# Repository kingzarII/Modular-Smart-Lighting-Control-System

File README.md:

# Modular-Smart-Lighting-Control-System

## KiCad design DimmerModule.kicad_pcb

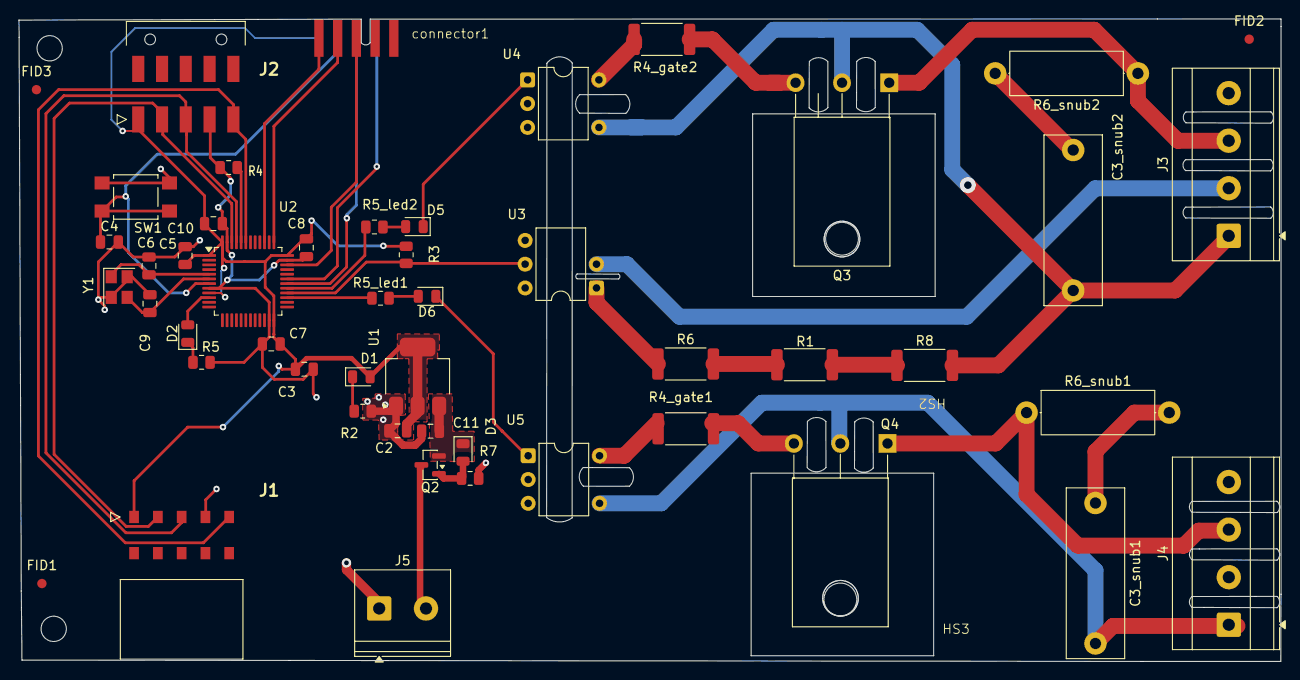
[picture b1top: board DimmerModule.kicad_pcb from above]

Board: 2 copper layers, 134.8 x 68.6 mm, 54 parts (0 on the bottom side), 41 nets.

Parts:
C2, C11: 22u; C_0805_2012Metric
C3: 10uF; C_0805_2012Metric
C3_snub1, C3_snub2: 100nF; C_Rect_L18.0mm_W6.0mm_P15.00mm_FKS3_FKP3
C4, C5, C7, C8: 100nF; C_0805_2012Metric
C6, C9: 10pF; C_0805_2012Metric
C10: 100n; C_0805_2012Metric
D1: LED; D_0805_2012Metric
D2: LED; LED_0805_2012Metric
D3: D_Zener; D_0805_2012Metric
D5, D6: RED; LED_0805_2012Metric
FID1, FID2, FID3: Fiducial; Fiducial_1mm_Mask2mm
H1, H1#2: MountingHole; MountingHole_2.7mm_M2.5
HS2, HS3: Heatsink; cooler
J1: Conn_01x05_Socket; 1156901
J2: Conn_01x05_Pin; 1156939
J3, J4: Screw_Terminal_01x04; TerminalBlock_Phoenix_MKDS-3-4-5.08_1x04_P5.08mm_Horizontal
J5: Screw_Terminal_01x02; TerminalBlock_Phoenix_PT-1,5-2-5.0-H_1x02_P5.00mm_Horizontal
Q2: AO3401A; SOT-23
Q3, Q4: BTA16-800B; TO-220-3_Horizontal_TabDown
R1, R8: 15KΩ; R_2512_6332Metric
R2, R5: 1.5K; R_0805_2012Metric
R3: 10kΩ; R_0805_2012Metric
R4, R7: 10K; R_0805_2012Metric
R4_gate1, R4_gate2: 180Ω; R_2512_6332Metric
R5_led1, R5_led2: 150Ω; R_0805_2012Metric
R6: 15kΩ; R_2512_6332Metric
R6_snub1, R6_snub2: 100Ω; R_Axial_DIN0414_L11.9mm_D4.5mm_P15.24mm_Horizontal
SW1: SW_Push; SW_SPST_TL3305B
U1: AMS1117-3.3; SOT-223-3_TabPin2
U2: STM32F103C8T6; LQFP-48_7x7mm_P0.5mm
U3: H11AA1; DIP-6_W7.62mm
U4, U5: MOC3021M; DIP-6_W7.62mm
Y1: 16Mhz; Crystal_SMD_3225-4Pin_3.2x2.5mm
connector1: Open Ended Card Edge

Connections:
+3.3V: C2.1, C3.1, C5.1, C7.1, C8.1, C10.1, D1.2 (A), J1.1, J2.1, R3.1, U1.2 (VO), U2.1 (VBAT), U2.9 (VDDA), U2.24 (VDD), U2.36 (VDD), U2.48 (VDD), connector1.10 (VCC)
+5V: C11.1, D3.1 (K), Q2.2 (S), U1.3 (VI)
/HSE_IN: C6.1, U2.5 (PD0), Y1.1
/HSE_OUT: C9.1, U2.6 (PD1), Y1.3
/Live: C3_snub2.2, J3.1, Q3.2 (A2), R8.2, U4.4
/Live1: C3_snub1.2, J4.1, Q4.2 (A2), U5.4
/Load: J3.3, Q3.1 (A1), R6_snub2.1
/Load2: J4.3, Q4.1 (A1), R6_snub1.1
/NRST: C4.1, SW1.1, U2.7 (NRST), connector1.9 (NRST)
/Neutral1: J3.2, U3.2
/SWCLK: U2.37 (PA14), connector1.4 (SWCLK)
/SWDIO: U2.34 (PA13), connector1.3 (SWDIO)
Enable: J1.5, J2.5, U2.43 (PB7)
GND: C2.2, C3.2, C4.2, C5.2, C6.2, C7.2, C8.2, C9.2, C10.2, C11.2, J1.4, J2.4, J5.1, R2.2, R4.2, R5.2, R7.2, SW1.2, U1.1 (GND), U2.8 (VSSA), U2.23 (VSS), U2.35 (VSS), U2.47 (VSS), U3.4, U4.2, U5.2, Y1.2, Y1.4, connector1.6 (GND)
unnamed: C3_snub1.1, R6_snub1.2
unnamed: C3_snub2.1, R6_snub2.2
unnamed: D1.1 (K), R2.1
unnamed: D2.2 (A), U2.10 (PA0)
unnamed: D2.1 (K), R5.1
unnamed: D3.2 (A), Q2.1 (G), R7.1
unnamed: D5.2 (A), R5_led2.2
unnamed: D5.1 (K), U4.1
unnamed: D6.2 (A), R5_led1.2
unnamed: D6.1 (K), U5.1
unnamed: J5.2, Q2.3 (D)
unnamed: Q3.3 (G), R4_gate2.1
unnamed: Q4.3 (G), R4_gate1.1
unnamed: R1.1, R6.2
unnamed: R1.2, R8.1
unnamed: R4_gate1.2, U5.6
unnamed: R4_gate2.2, U4.6
unnamed: R6.1, U3.1
unnamed: R4.1, U2.44 (BOOT0)
SCL_IN: J1.3, J2.3, U2.45 (PB8)
SDA_IN: J1.2, J2.2, U2.46 (PB9)
SWO: U2.39 (PB3), connector1.5 (SWO)
rx: U2.30 (PA9), connector1.8 (TX)
triac1: R5_led2.1, U2.29 (PA8)
triac2: R5_led1.1, U2.27 (PB14)
tx: U2.31 (PA10), connector1.7 (RX)
zero1: R3.2, U2.28 (PB15), U3.5

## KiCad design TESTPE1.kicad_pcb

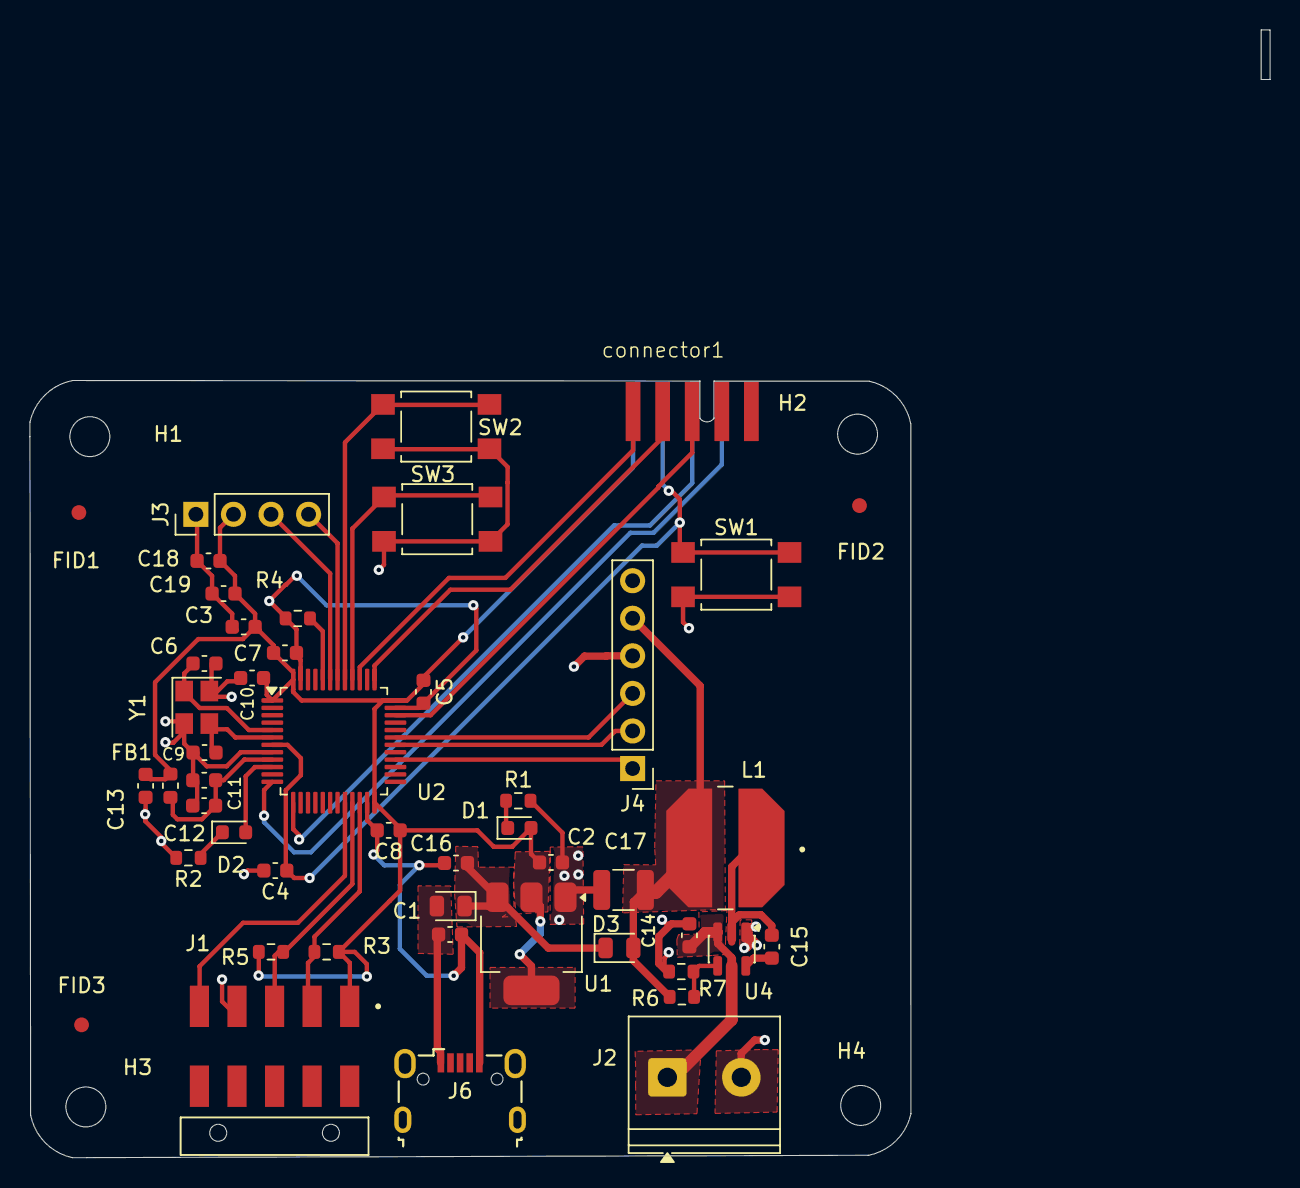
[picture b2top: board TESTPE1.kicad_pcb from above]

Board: 2 copper layers, 59.6 x 52.5 mm, 52 parts (0 on the bottom side), 32 nets.

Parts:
C1, C2, C16: 22u; C_0603_1608Metric
C3: 10uF; C_0603_1608Metric
C4, C5, C7, C8, C10, C15: 100n; C_0603_1608Metric
C6, C9: 10pF; C_0603_1608Metric
C11: 10n; C_0603_1608Metric
C12, C13: 1u; C_0603_1608Metric
C14: 2.2uF; C_0603_1608Metric
C17: 44uF; C_1210_3225Metric
C18: 100nF; C_0603_1608Metric
C19: 1uF; C_0603_1608Metric
D1, D2: RED; LED_0603_1608Metric
D3, D4: D; D_0805_2012Metric
FB1: FerriteBead; L_0603_1608Metric
FID1, FID2, FID3: Fiducial; Fiducial_1mm_Mask2mm
H1, H2, H3, H4: MountingHole; MountingHole_2.7mm_M2.5
J1: 1156939; PHOENIX_1156939
J2: Screw_Terminal_01x02; TerminalBlock_Phoenix_PT-1,5-2-5.0-H_1x02_P5.00mm_Horizontal
J3: Conn_01x04_Pin; PinHeader_1x04_P2.54mm_Vertical
J4: Conn_01x06_Pin; PinHeader_1x06_P2.54mm_Vertical
J6: USB_B_Micro; USB_Micro-B_Wuerth_629105150521
L1: 6.8uH; IND_1273AS-H-6R8N=P3
R1, R2: 1K5; R_0603_1608Metric
R3, R5: 1K; R_0603_1608Metric
R4: 10K; R_0603_1608Metric
R6: 100K; R_0603_1608Metric
R7: 13.7K; R_0603_1608Metric
SW1, SW2, SW3: SW_Push; SW_SPST_TL3305B
U1: AMS1117-3.3; SOT-223-3_TabPin2
U2: STM32F103C8T6; LQFP-48_7x7mm_P0.5mm
U4: LMR51430; SOT-23-6
Y1: 16Mhz; Crystal_SMD_3225-4Pin_3.2x2.5mm
connector1: Open Ended Card Edge

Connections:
+3.3V: C2.1, C3.1, C5.1, C7.1, C8.1, C10.1, C13.1, C18.1, C19.1, D1.2 (A), FB1.1, J1.01, J3.2, R3.1, R5.1, U1.2 (VO), U2.1 (VBAT), U2.24 (VDD), U2.36 (VDD), U2.48 (VDD), connector1.10 (VCC)
+3.3VA: C11.1, C12.1, FB1.2, U2.9 (VDDA)
+5V: C17.1, D3.2 (A), J4.5, L1.2, R6.1
+12V: C14.1, J2.1, U4.3 (VIN), U4.5 (EN)
/HSE_IN: C6.1, U2.5 (PD0), Y1.1
/HSE_OUT: C9.1, U2.6 (PD1), Y1.3
/NRST: C4.1, SW1.1, U2.7 (NRST), connector1.9 (NRST)
/SWCLK: U2.37 (PA14), connector1.4 (SWCLK)
/SWDIO: U2.34 (PA13), connector1.3 (SWDIO)
GND: C1.2, C2.2, C3.2, C4.2, C5.2, C6.2, C7.2, C8.2, C9.2, C10.2, C11.2, C12.2, C13.2, C14.2, C16.2, C17.2, C18.2, C19.2, J1.04, J2.2, J3.1, J4.4, J6.5 (GND), R1.2, R2.2, R4.2, R7.2, SW1.2, SW2.2, SW3.2, U1.1 (GND), U2.8 (VSSA), U2.23 (VSS), U2.35 (VSS), U2.47 (VSS), U4.1 (GND), Y1.2, Y1.4, connector1.6 (GND)
unnamed: D1.1 (K), R1.1
unnamed: D2.2 (A), U2.10 (PA0)
unnamed: D2.1 (K), R2.1
unnamed: R4.1, U2.44 (BOOT0)
unnamed: C15.1, U4.6 (CB)
unnamed: R6.2, R7.1, U4.4 (FB)
unnamed: C15.2, L1.1, U4.2 (SW)
SWO: U2.39 (PB3), connector1.5 (SWO)
VBUS: C1.1, D4.2 (A), J6.1 (VBUS)
enable: J1.05, U2.20 (PB2)
rx: J4.2, U2.30 (PA9)
rx1: U2.12 (PA2), connector1.7 (RX)
scl: J3.3, U2.43 (PB7)
scl1: J1.03, R5.2, U2.21 (PB10)
sda: J3.4, U2.42 (PB6)
sda1: J1.02, R3.2, U2.22 (PB11)
state: J4.1, U2.28 (PB15)
switch1: SW2.1, U2.41 (PB5)
switch2: SW3.1, U2.40 (PB4)
tx: J4.3, U2.31 (PA10)
tx1: U2.13 (PA3), connector1.8 (TX)
vin: C16.1, D3.1 (K), D4.1 (K), U1.3 (VI)
